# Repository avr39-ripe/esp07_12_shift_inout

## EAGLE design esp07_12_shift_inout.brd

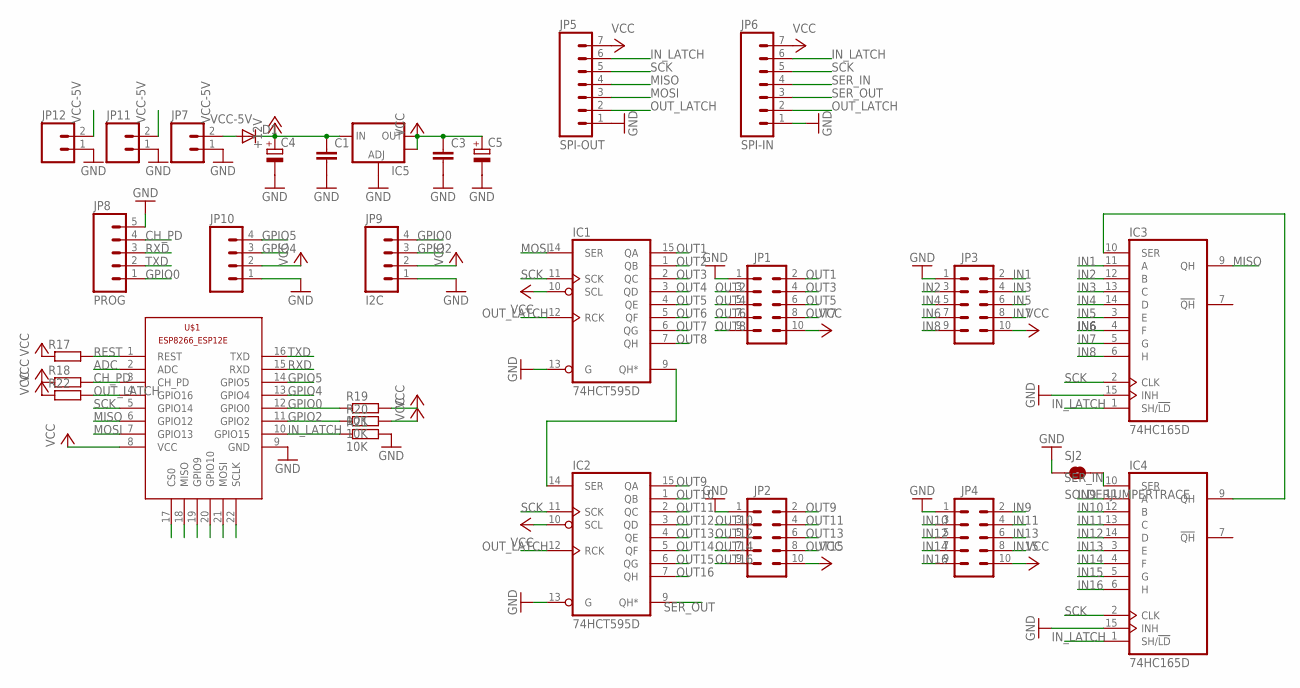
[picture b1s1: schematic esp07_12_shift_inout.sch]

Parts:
C1, C3: C-EUC0805; C0805
C4, C5: CPOL-EUD/7343-31R; D/7343-31R
D1: DIODE-DO214AC; DO214AC
IC1, IC2: 74HCT595D; SO16
IC3, IC4: 74HC165D; SO16
IC5: V_REG_LM1117SOT223; SOT223
JP1, JP2, JP3, JP4: M05X2SHD; 2X5-SHROUDED
JP5: SPI-OUT; 1X07
JP6: SPI-IN; 1X07
JP7: M02PTH3; 1X02_LONGPADS
JP8: PROG; 1X05
JP9: I2C; 1X04
JP10: M04PTH; 1X04
JP11, JP12: M02PTH; 1X02
R17, R18, R22: R-EU_R0603; R0603
R19, R20, R21: 10K; R0603
SJ2: SOLDERJUMPERTRACE; SJ_2S-TRACE
U$1: ESP8266-12EESP8266-ESP12E; ESP8266-ESP12E

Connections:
+12V: C1.1, C4.+, D1.C, IC5.3 (IN)
ADC: U$1.2 (ADC)
CH_PD: JP8.4, R18.2, U$1.3 (CH_PD)
GND: C1.2, C3.2, C4.-, C5.-, IC1.8 (GND), IC1.13 (G), IC2.8 (GND), IC2.13 (G), IC3.8 (GND), IC3.15 (INH), IC4.8 (GND), IC4.15 (INH), IC5.1 (ADJ), JP1.1, JP2.1, JP3.1, JP4.1, JP5.1, JP6.1, JP7.1, JP8.5, JP9.1, JP10.1, JP11.1, JP12.1, R21.2, SJ2.1, U$1.9 (GND)
GPIO0: JP8.1, JP9.4, R19.1, U$1.12 (GPIO0)
GPIO2: JP9.3, R20.1, U$1.11 (GPIO2)
GPIO4: JP10.3, U$1.13 (GPIO4)
GPIO5: JP10.4, U$1.14 (GPIO5)
IN1: IC3.11 (A), JP3.2
IN2: IC3.12 (B), JP3.3
IN3: IC3.13 (C), JP3.4
IN4: IC3.14 (D), JP3.5
IN5: IC3.3 (E), JP3.6
IN6: IC3.4 (F), JP3.7
IN7: IC3.5 (G), JP3.8
IN8: IC3.6 (H), JP3.9
IN9: IC4.11 (A), JP4.2
IN10: IC4.12 (B), JP4.3
IN11: IC4.13 (C), JP4.4
IN12: IC4.14 (D), JP4.5
IN13: IC4.3 (E), JP4.6
IN14: IC4.4 (F), JP4.7
IN15: IC4.5 (G), JP4.8
IN16: IC4.6 (H), JP4.9
IN_LATCH: IC3.1 (SH/!LD), IC4.1 (SH/!LD), JP5.6, JP6.6, R21.1, U$1.10 (GPIO15)
MISO: IC3.9 (QH), JP5.4, U$1.6 (GPIO12)
MOSI: IC1.14 (SER), JP5.3, U$1.7 (GPIO13)
unnamed: IC1.9 (QH*), IC2.14 (SER)
unnamed: IC3.10 (SER), IC4.9 (QH)
OUT1: IC1.15 (QA), JP1.2
OUT2: IC1.1 (QB), JP1.3
OUT3: IC1.2 (QC), JP1.4
OUT4: IC1.3 (QD), JP1.5
OUT5: IC1.4 (QE), JP1.6
OUT6: IC1.5 (QF), JP1.7
OUT7: IC1.6 (QG), JP1.8
OUT8: IC1.7 (QH), JP1.9
OUT9: IC2.15 (QA), JP2.2
OUT10: IC2.1 (QB), JP2.3
OUT11: IC2.2 (QC), JP2.4
OUT12: IC2.3 (QD), JP2.5
OUT13: IC2.4 (QE), JP2.6
OUT14: IC2.5 (QF), JP2.7
OUT15: IC2.6 (QG), JP2.8
OUT16: IC2.7 (QH), JP2.9
OUT_LATCH: IC1.12 (RCK), IC2.12 (RCK), JP5.2, JP6.2, R22.2, U$1.4 (GPIO16)
REST: R17.2, U$1.1 (REST)
RXD: JP8.3, U$1.15 (RXD)
SCK: IC1.11 (SCK), IC2.11 (SCK), IC3.2 (CLK), IC4.2 (CLK), JP5.5, JP6.5, U$1.5 (GPIO14)
SER_IN: IC4.10 (SER), JP6.4, SJ2.2
SER_OUT: IC2.9 (QH*), JP6.3
TXD: JP8.2, U$1.16 (TXD)
VCC: C3.1, C5.+, IC1.10 (SCL), IC1.16 (VCC), IC2.10 (SCL), IC2.16 (VCC), IC3.16 (VCC), IC4.16 (VCC), IC5.2 (OUT), IC5.4 (OUT), JP1.10, JP2.10, JP3.10, JP4.10, JP5.7, JP6.7, JP9.2, JP10.2, R17.1, R18.1, R19.2, R20.2, R22.1, U$1.8 (VCC)
VCC-5V: D1.A, JP7.2, JP11.2, JP12.2

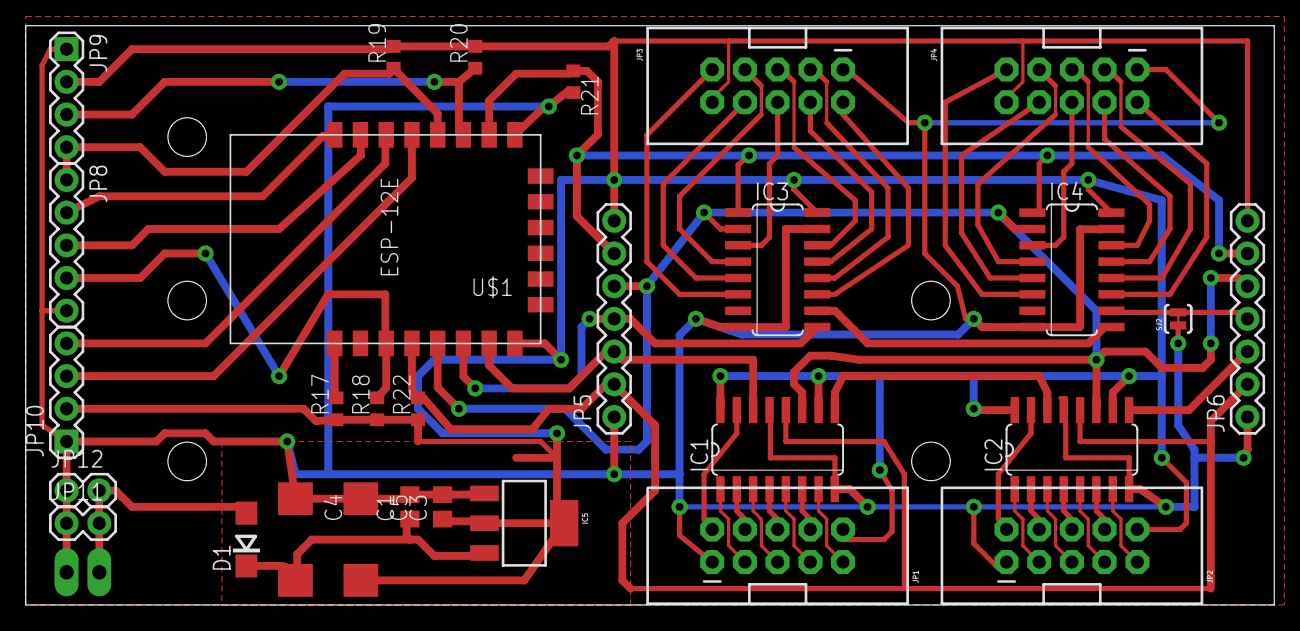
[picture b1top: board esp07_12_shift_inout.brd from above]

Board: 2 copper layers, 97.0 x 45.0 mm, 30 parts (0 on the bottom side), 53 nets.

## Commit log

2015-09-06 Another approximation
2015-09-06 Almost good variant mounting holes and polygon pour are missing
2015-09-06 First version vhich will go to production
2015-09-11 Add TODO and .gitignore. Write some future task in TODO
2015-10-21 * Add .gitignore
2015-10-21 * Change ESP module to ESP-12E footprint. Change ESP resistors to 0603. Change *_LATCH pins to 15,16
2015-10-21 * Change OUT connectors to 2x10 and add GND / VCC pins to them
2015-10-22 * Change OUT pins configuration to pin 1 - GND, pin 10 - VCC
2015-10-22 * Finish new version of PCB.
    * Change ESP module to ESP-12E with additional (but useless) pins
    * Change OUT_ IN_ latch to 15,16
    * Change OUT_ IN_ connection to 2x5 header
    * Remove pull-up resistors on IN_ part in favour to implement them in add-on opto-isolated IN PCB

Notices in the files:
parts and their libraries:
SparkFun-Connectors: Licensing: Creative Commons ShareAlike 4.0 International - https://creativecommons.org/licenses/by-sa/4.0
